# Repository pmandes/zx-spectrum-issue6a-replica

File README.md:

# ZX Spectrum 48k Issue 6A board replica

This is PCB replica of the motherboard of a ZX Spectrum 48k 8-bit computer. It was created on the basis of the last version of the board - "ISSUE 6A" - which was mounted in both Spectrum 48k and Spectrum+. It differs from previous versions mainly by integrating the logic and memory multiplexers in one ZX8401 chip, as well as an improved (especially in comparison with the first versions) the power supply circuit.

## The purpose of the project

I created it as a tribute to this wonderful little computer for the 40th anniversary of its creation, which for many of us started the adventure in the world of IT technology. Thanks to this replica, you can repair your old ZX Spectrum in which the connector contacts have worn off, tracks and pads have torn off after numerous repairs or have simply been destroyed by rust. After transplanting components to a new board, your Spectrum will not only gain a new life, but also a great look.

### The ISSUE 6A board requires the following components:

- Zilog Z80 processor
- ZX8401 / PCF1306P chip - or its cheap direct replacement built on SMD 74LS chips
- ULA in any version (originally on this board was Ferranti 6C001E-7) or a perfect, modern replacement vLA82
- original ZX Spectrum ROM or EPROM 27C256/27C512 with programmed BASIC binary (requires a slight modification or adapter, e.g. [ZXROM 4-in-1](https://github.com/pmandes/zx-spectrum-issue6a-replica/tree/main/ZX-ROM-4-in-1))
- lower memory chips type 4116 (e.g. TMS4116-15NL, STC 4116-2N) or a modern SRAM replacement board
- upper memory chips type 4532 or compatible (e.g. TMS 4532-20NL4, OKI M3764-20RS) or modern SRAM module
- LM1889 video modulation chip
- UM1233 RF modulator or S-VIDEO mod board or simple composite output mod

## BOM:

https://docs.google.com/spreadsheets/d/1GlukvK-rJ6DSs6qOmtWpRyai1MQ1hy25GcS9ePSdg4E/edit?usp=sharing

- The resistor and capacitor values in the BOM file are for Ferranti ULA
- For a standard Ferranti ULA - **do not populate: R90, C100, C102, C103**, leave LK1, LK2, LK3, LK4 - opened
- For SAGA chip - refer the Service Manual
- For TMS chips on upper memory: TI - close, 3 or 4 - depends on the marking on the chip: i.e. TMS4532-20NL**4**
- For OKI chip on upper memory: OKI - close, L or H - depends on the marking on the chip: i.e. OKI3732**L**-20RS, for OKI3764 - you can choose which 'half' of its 64kbit you want to use
- ROM settings: N - close for NEC chips, H - for HITACHI chips, for the EPROM adapter - it does not matter

**Correct jumper configuration near IC28:**

**Interactive BOM:**
<p align="center"></p>

**Notice:**

I received reports that the board version 1.1 (Dec 2022) has too small holes for the original **BA157** diodes (D15 and D17) - I used **BA159** diodes manufactured by **MIC** in the DO-41 package. They have 0.55mm / 0.0215inch thick legs - they fit and work perfectly.

## Motherboard layout:
https://github.com/pmandes/zx-spectrum-issue6a-replica/blob/main/Issue-6A-layout.pdf

## Changelog:

**1.2**
- enlargement of all solder holes up to 0.8mm, holes for D15/D17 diodes up to 1mm

**1.1**
- improving the position of the mounting holes
- correction of all mistakes detected on the prototype

**1.0**
- prototype

## PCBs:

Here you can order ready-made, unpopulated PCBs:

https://www.tindie.com/products/devzine_pl/zx-spectrum-48k-issue-6a-motherboard-replica-pcbs/

## ROMs:

- https://mdfs.net/Software/Spectrum/ROMImages/
- https://github.com/brendanalford/zx-diagnostics
- http://blog.retroleum.co.uk/electronics-articles/a-diagnostic-rom-image-for-the-zx-spectrum/

## Alternative components:

- PCF1306P / ZX8401: https://trastero.speccy.org/cosas/JL/pcf1306p/PCF1306P.html
- PCF1306P SMD: https://www.va-de-retro.com/foros/viewtopic.php?p=182085#p182085
- S-Video Mod: https://github.com/redhawk668/ZX-Spectrum-S-Video
- Composite Mod: https://github.com/lostretrotapes/ProjectSpeccy-Sinclair-Spectrum-Composite-Mod-PCB
## Useful resources:
- Schematics: https://spectrumforeveryone.com/technical/zx-spectrum-pcb-schematics-layout/
- Service manual: https://spectrumforeveryone.com/wp-content/uploads/2017/08/ZX-Spectrum-Service-Manual.pdf
 
---

All material published here is under a [Creative Commons 4.0 license](https://creativecommons.org/licenses/by-nc-nd/4.0/).

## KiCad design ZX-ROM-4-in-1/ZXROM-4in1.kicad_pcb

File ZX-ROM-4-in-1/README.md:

# ZXROM 4-in-1
## 27C512 EPROM adapter for ZX Spectrum 48K

### Bill of materials:

<p align="center">

</p>

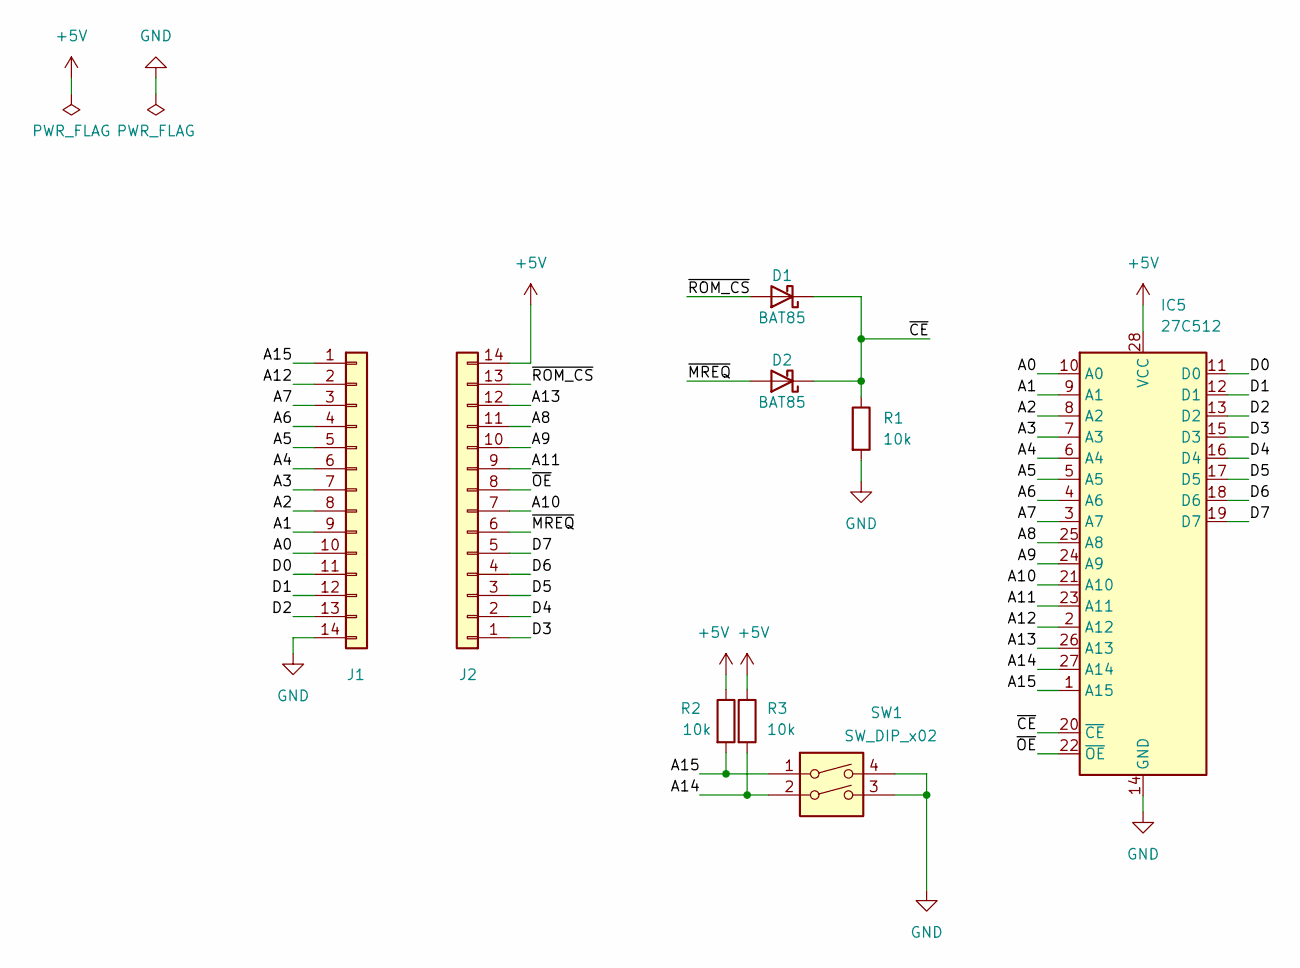
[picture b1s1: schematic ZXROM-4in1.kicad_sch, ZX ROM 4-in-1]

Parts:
D1, D2: BAT85; D_DO-35_SOD27_P7.62mm_Horizontal
IC5: 27C512; DIP-28_W15.24mm
J1, J2: Conn_01x14; PinHeader_1x14_P2.54mm_Vertical
R1, R2, R3: 10k; R_Axial_DIN0207_L6.3mm_D2.5mm_P7.62mm_Horizontal
SW1: SW_DIP_x02; SW_DIP_SPSTx02_Slide_9.78x7.26mm_W7.62mm_P2.54mm

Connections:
+5V: IC5.28 (VCC), J2.14, R2.1, R3.1
/A0: IC5.10 (A0), J1.10
/A1: IC5.9 (A1), J1.9
/A2: IC5.8 (A2), J1.8
/A3: IC5.7 (A3), J1.7
/A4: IC5.6 (A4), J1.6
/A5: IC5.5 (A5), J1.5
/A6: IC5.4 (A6), J1.4
/A7: IC5.3 (A7), J1.3
/A8: IC5.25 (A8), J2.11
/A9: IC5.24 (A9), J2.10
/A10: IC5.21 (A10), J2.7
/A11: IC5.23 (A11), J2.9
/A12: IC5.2 (A12), J1.2
/A13: IC5.26 (A13), J2.12
/A14: IC5.27 (A14), R3.2, SW1.2
/A15: IC5.1 (A15), J1.1, R2.2, SW1.1
/D0: IC5.11 (D0), J1.11
/D1: IC5.12 (D1), J1.12
/D2: IC5.13 (D2), J1.13
/D3: IC5.15 (D3), J2.1
/D4: IC5.16 (D4), J2.2
/D5: IC5.17 (D5), J2.3
/D6: IC5.18 (D6), J2.4
/D7: IC5.19 (D7), J2.5
/~CE: D1.1 (K), D2.1 (K), IC5.20 (~CE), R1.1
/~MREQ: D2.2 (A), J2.6
/~OE: IC5.22 (~OE), J2.8
/~ROM_CS: D1.2 (A), J2.13
GND: IC5.14 (GND), J1.14, R1.2, SW1.3, SW1.4

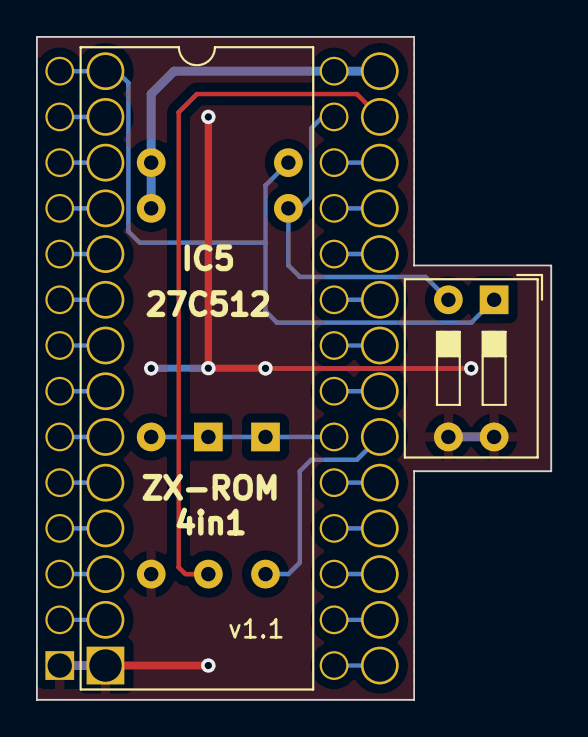
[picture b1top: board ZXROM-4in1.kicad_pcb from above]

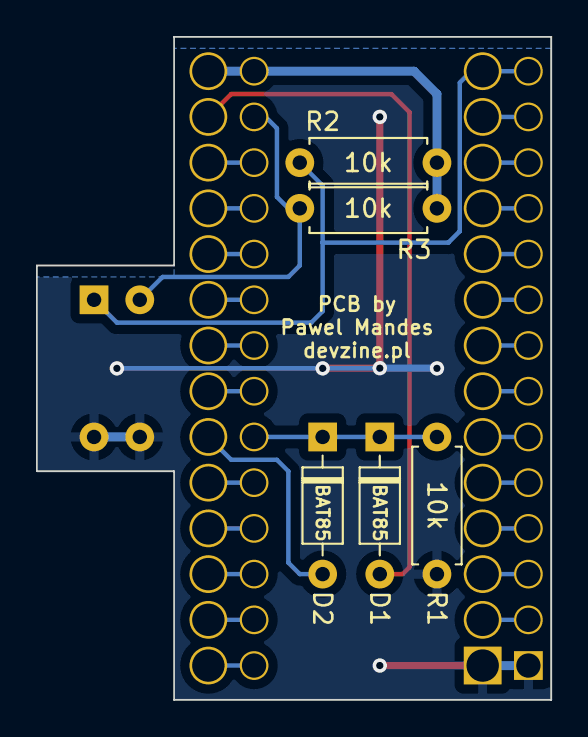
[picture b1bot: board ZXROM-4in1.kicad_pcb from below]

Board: 2 copper layers, 28.6 x 36.8 mm, 9 parts (5 on the bottom side), 30 nets.

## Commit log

2022-12-19 ZXROM v1.0 initial commit, ISSUE 6A docs
2022-12-19 BOM for ZXROM
2023-01-10 New images, and adapter update
2023-01-13 Layout image added
2023-07-15 new images
2023-08-11 New pcb 3D render
2023-08-11 interactive BOM, and updated BOM file
2023-08-11 bom image
2023-10-08 version 1.1
